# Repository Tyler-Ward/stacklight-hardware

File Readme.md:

POE Stack Light PCB design
==========================

The [POE stack light][blog-post] is a network controlled status indication light that is powered over the network using POE.

This repository contains the Kicad schematic and PCB design for the project, the [firmware][firmware-repo] and [documentation and build guide][documentation-repo] can be found in their respective git repositories.

Circuit Overview
---------------

The design is split into four major sections, the output stage, the POE power supply, the processor, and the network interface.

The stack light takes a common 12v input with switched grounds for each light segment and the buzzer.
A mosfet is used to control each of the channels, brightness is controlled by PWM from the microcontroller.
As supplied the light has a voltage regulator based current limiter shared across all the illumination channels, this prevents multiple segments from being lit at full brightness simultaneously.
This is resolved by bypassing the current limit inside the light with a jumper wire and then adding a copy of the current limiter circuit in the light to the board for each of the three led channels, giving them their own current limit.
See the assembly documentation for how to modify the stack light do this.

For the POE power input, a transformer setup rather than a switch mode design is used.
The use of a transformer based design provides electrical isolation and allows other connections to be exposed without the risk of a short.
The power over ethernet schematic is based on the MP8007 reference design.
A backup DC jack is also available if wanting to build without POE.

An integrated ESP32 wireless module is used for the main processor.
The network interface uses the LAN8710A ethernet transceiver IC.
This communicates to the ESP32 with the RMII protocol used for 100MB ethernet PHYs.
A USB to serial converter is included to facilitate easy programming.

[blog-post]: https://www.scorpia.co.uk/2021/05/23/building-a-poe-enabled-lighting-fixture/
[firmware-repo]: https://github.com/Tyler-Ward/stacklight-firmware
[documentation-repo]: https://github.com/Tyler-Ward/stacklight-documentation

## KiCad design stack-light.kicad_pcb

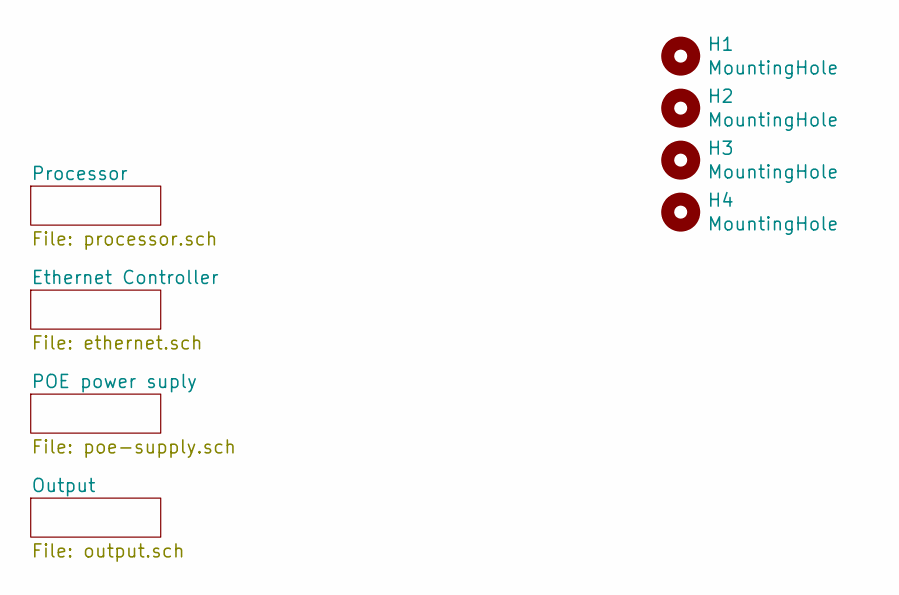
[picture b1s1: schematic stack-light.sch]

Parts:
H1, H2, H3, H4: MountingHole; MountingHole_3.2mm_M3

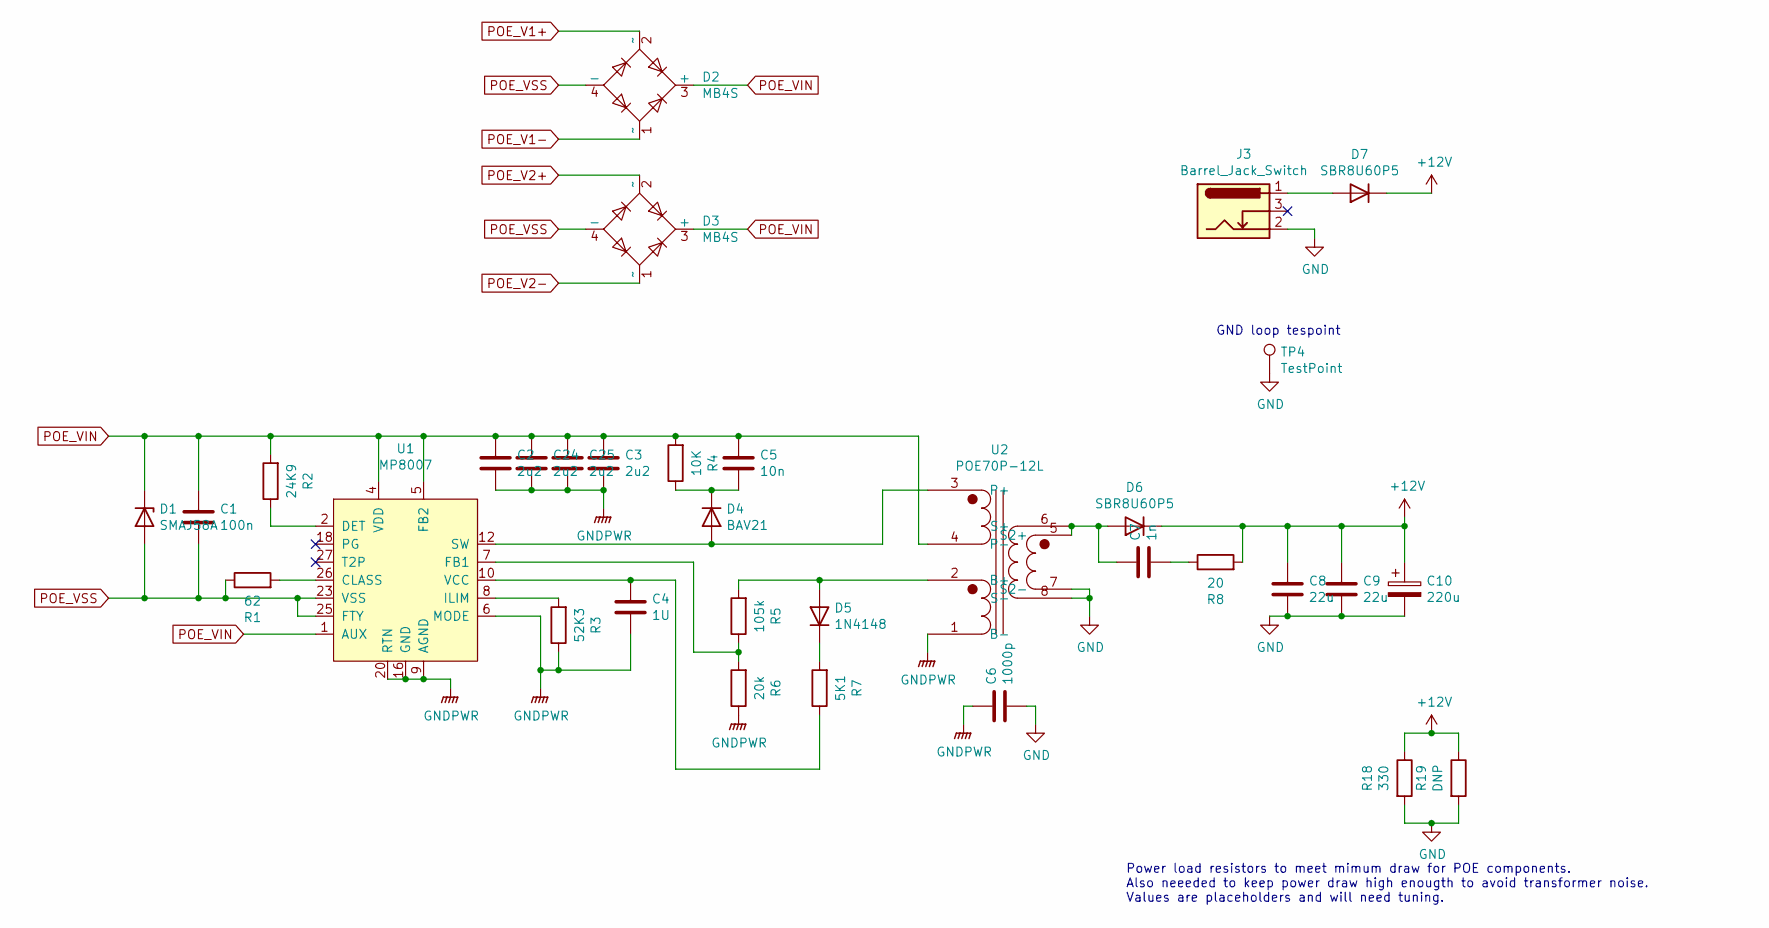
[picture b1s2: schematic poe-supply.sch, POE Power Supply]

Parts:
C1: 100n; C_1206_3216Metric
C2, C3, C24, C25: 2u2; C_1210_3225Metric
C4: 1U; C_0603_1608Metric
C5: 10n; C_0805_2012Metric
C6: 1000p; C_1806_4516Metric
C7: 1n; C_0603_1608Metric
C8, C9: 22u; C_1210_3225Metric
C10: 220u; CP_EIA-7343-31_Kemet-D
D1: SMAJ58A; D_SMA
D2, D3: MB4S; TO-269AA
D4: BAV21; D_SOD-123
D5: 1N4148; D_SOD-323
D6, D7: SBR8U60P5; D_PowerDI-5
J3: Barrel_Jack_Switch; BarrelJack_Horizontal
R1: 62; R_0603_1608Metric
R2: 24K9; R_0603_1608Metric
R3: 52K3; R_0603_1608Metric
R4: 10K; R_1206_3216Metric
R5: 105k; R_0603_1608Metric
R6: 20k; R_0603_1608Metric
R7: 5K1; R_0603_1608Metric
R8: 20; R_0805_2012Metric
R18: 330; R_1210_3225Metric
R19: DNP; R_1210_3225Metric
TP4: TestPoint; TestPoint_Bridge_Pitch5.08mm_Drill0.7mm
U1: MP8007; QFN-28-1EP_4x5mm_P0.5mm_EP2.65x3.65mm
U2: POE70P-12L; Transformer_Coilcraft_POE70P

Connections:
+12V: C8.1, C9.1, C10.1, D6.1 (K), D7.1 (K), R8.2, R18.1, R19.1; also elsewhere on the board
GND: C6.2, C8.2, C9.2, C10.2, J3.2, R18.2, R19.2, TP4.1, U2.7 (S2-), U2.8 (S-); also elsewhere on the board
GNDPWR: C2.2, C3.2, C4.2, C6.1, C24.2, C25.2, R3.1, R6.1, U1.6 (MODE), U1.9 (AGND), U1.16 (GND), U1.17, U1.20 (RTN), U1.21, U1.29 (GND), U2.1 (B-)
unnamed: C4.1, R7.1, U1.10 (VCC)
unnamed: C5.2, D4.1 (K), R4.1
unnamed: C7.1, D6.2 (A), U2.5 (S2+), U2.6 (S+)
unnamed: C7.2, R8.1
unnamed: D4.2 (A), U1.12 (SW), U1.13, U2.3 (P+)
unnamed: D5.1 (K), R7.2
unnamed: D5.2 (A), R5.2, U2.2 (B+)
unnamed: D7.2 (A), J3.1
unnamed: R1.2, U1.26 (CLASS)
unnamed: R2.1, U1.2 (DET)
unnamed: R3.2, U1.8 (ILIM)
unnamed: R5.1, R6.2, U1.7 (FB1)
POE_V1+: D2.2 (~~); also elsewhere on the board
POE_V1-: D2.1 (~~); also elsewhere on the board
POE_V2+: D3.2 (~~); also elsewhere on the board
POE_V2-: D3.1 (~~); also elsewhere on the board
POE_VIN: C1.1, C2.1, C3.1, C5.1, C24.1, C25.1, D1.1 (K), D2.3 (+), D3.3 (+), R2.2, R4.2, U1.1 (AUX), U1.4 (VDD), U1.5 (FB2), U2.4 (P-)
POE_VSS: C1.2, D1.2 (A), D2.4 (-), D3.4 (-), R1.1, U1.23 (VSS), U1.24, U1.25 (FTY)

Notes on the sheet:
Power load resistors to meet mimum draw for POE components. Also neeeded to keep power draw high enougth to avoid transformer noise. Values are placeholders and will need tuning.
GND loop tespoint

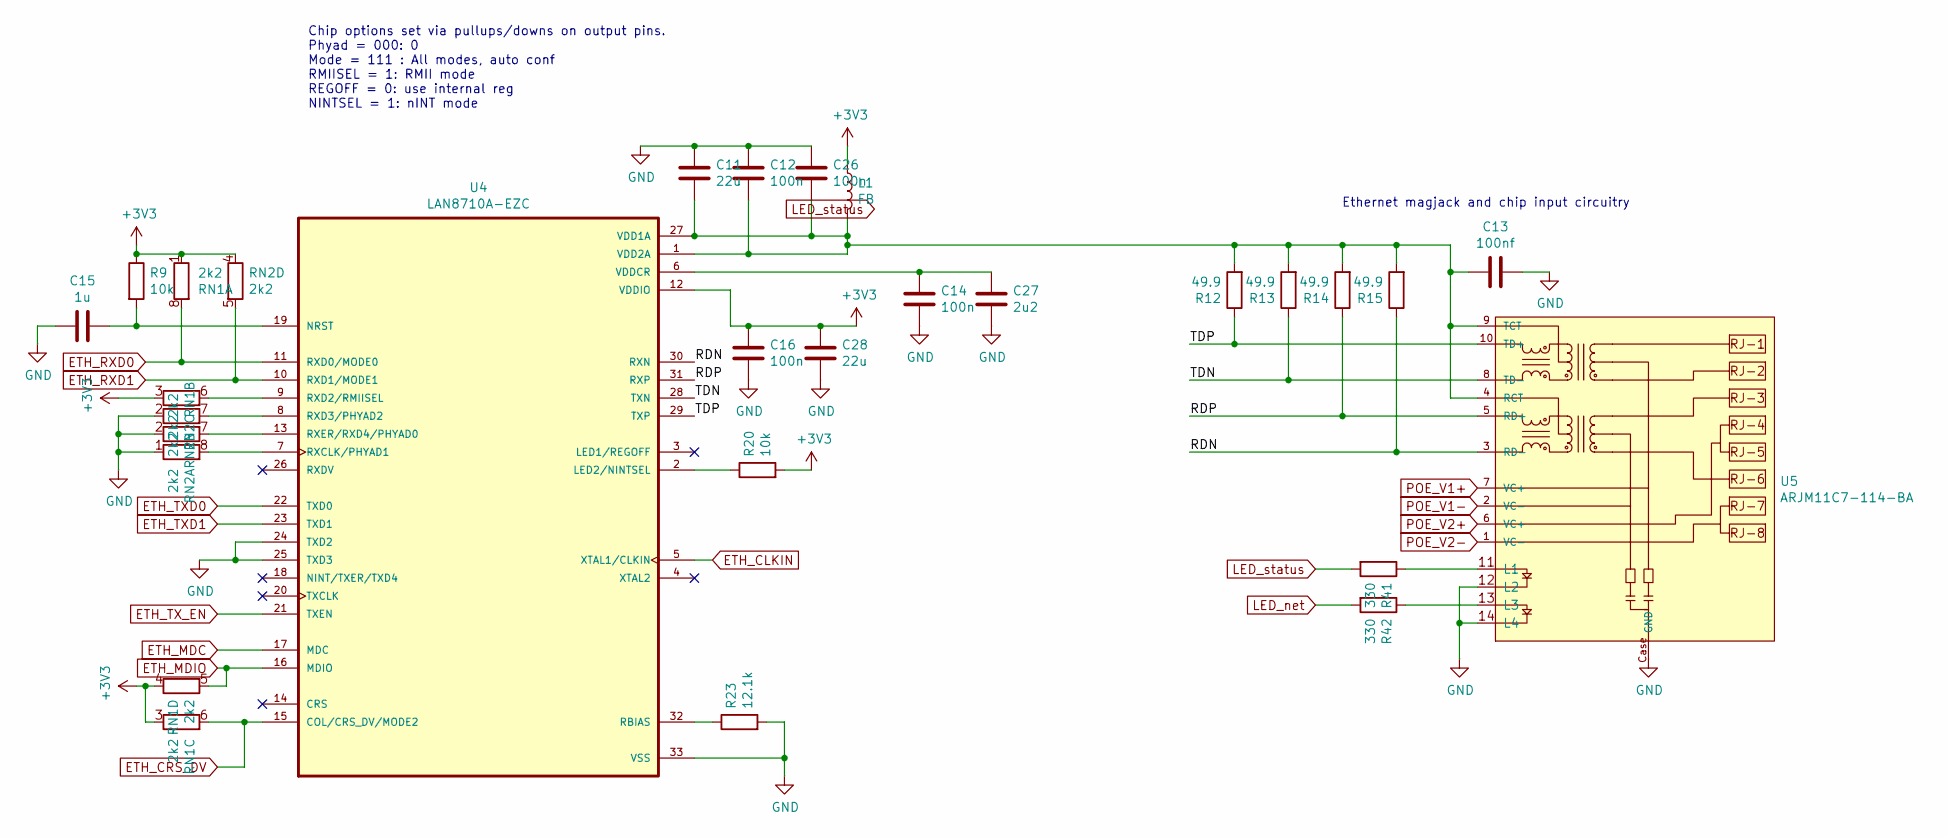
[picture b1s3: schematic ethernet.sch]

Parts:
C11, C28: 22u; C_0805_2012Metric
C12, C14, C16, C26: 100n; C_0603_1608Metric
C13: 100nf; C_0603_1608Metric
C15: 1u; C_0603_1608Metric
C27: 2u2; C_0603_1608Metric
L1: FB; L_0805_2012Metric
R9, R20: 10k; R_0603_1608Metric
R12, R13, R14, R15: 49.9; R_0603_1608Metric
R23: 12.1k; R_0603_1608Metric
R41, R42: 330; R_0603_1608Metric
RN1, RN2: 2k2; R_Array_Convex_4x0603
U4: LAN8710A-EZC; QFN-32-1EP_5x5mm_P0.5mm_EP3.3x3.3mm
U5: ARJM11C7-114-BA

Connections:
+3V3: C16.1, C28.1, L1.1, R9.1, R20.2, RN1.1 (R1.1), RN1.3 (R3.1), RN1.4 (R4.1), RN2.3 (R3.1), RN2.4 (R4.1), U4.12 (VDDIO); also elsewhere on the board
/Ethernet Controller/RDN: R15.1, U4.30 (RXN), U5.3 (RD-)
/Ethernet Controller/RDP: R14.1, U4.31 (RXP), U5.5 (RD+)
/Ethernet Controller/TDN: R13.1, U4.28 (TXN), U5.8 (TD-)
/Ethernet Controller/TDP: R12.1, U4.29 (TXP), U5.10 (TD+)
ETH_CLKIN: U4.5 (XTAL1/CLKIN); also elsewhere on the board
ETH_CRS_DV: RN1.6 (R3.2), U4.15 (COL/CRS_DV/MODE2); also elsewhere on the board
ETH_MDC: U4.17 (MDC); also elsewhere on the board
ETH_MDIO: RN1.5 (R4.2), U4.16 (MDIO); also elsewhere on the board
ETH_RXD0: RN1.8 (R1.2), U4.11 (RXD0/MODE0); also elsewhere on the board
ETH_RXD1: RN2.5 (R4.2), U4.10 (RXD1/MODE1); also elsewhere on the board
ETH_TXD0: U4.22 (TXD0); also elsewhere on the board
ETH_TXD1: U4.23 (TXD1); also elsewhere on the board
ETH_TX_EN: U4.21 (TXEN); also elsewhere on the board
GND: C11.1, C12.1, C13.1, C14.2, C15.2, C16.2, C26.1, C27.2, C28.2, R23.2, RN1.2 (R2.1), RN2.1 (R1.1), RN2.2 (R2.1), U4.24 (TXD2), U4.25 (TXD3), U4.33 (VSS), U5.12 (L2), U5.14 (L4), U5.Case (GND); also elsewhere on the board
LED_net: R42.2; also elsewhere on the board
LED_status: R41.2; also elsewhere on the board
unnamed: C11.2, C12.2, C13.2, C26.2, L1.2, R12.2, R13.2, R14.2, R15.2, U4.1 (VDD2A), U4.27 (VDD1A), U5.4 (RCT), U5.9 (TCT)
unnamed: C14.1, C27.1, U4.6 (VDDCR)
unnamed: C15.1, R9.2, U4.19 (NRST)
unnamed: R20.1, U4.2 (LED2/NINTSEL)
unnamed: R23.1, U4.32 (RBIAS)
unnamed: R41.1, U5.11 (L1)
unnamed: R42.1, U5.13 (L3)
unnamed: RN1.7 (R2.2), U4.13 (RXER/RXD4/PHYAD0)
unnamed: RN2.6 (R3.2), U4.9 (RXD2/RMIISEL)
unnamed: RN2.7 (R2.2), U4.8 (RXD3/PHYAD2)
unnamed: RN2.8 (R1.2), U4.7 (RXCLK/PHYAD1)
POE_V1+: U5.7 (VC+); also elsewhere on the board
POE_V1-: U5.2 (VC-); also elsewhere on the board
POE_V2+: U5.6 (VC+); also elsewhere on the board
POE_V2-: U5.1 (VC-); also elsewhere on the board

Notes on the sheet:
Ethernet magjack and chip input circuitry
Chip options set via pullups/downs on output pins. Phyad = 000: 0 Mode = 111 : All modes, auto conf RMIISEL = 1: RMII mode REGOFF = 0: use internal reg NINTSEL = 1: nINT mode

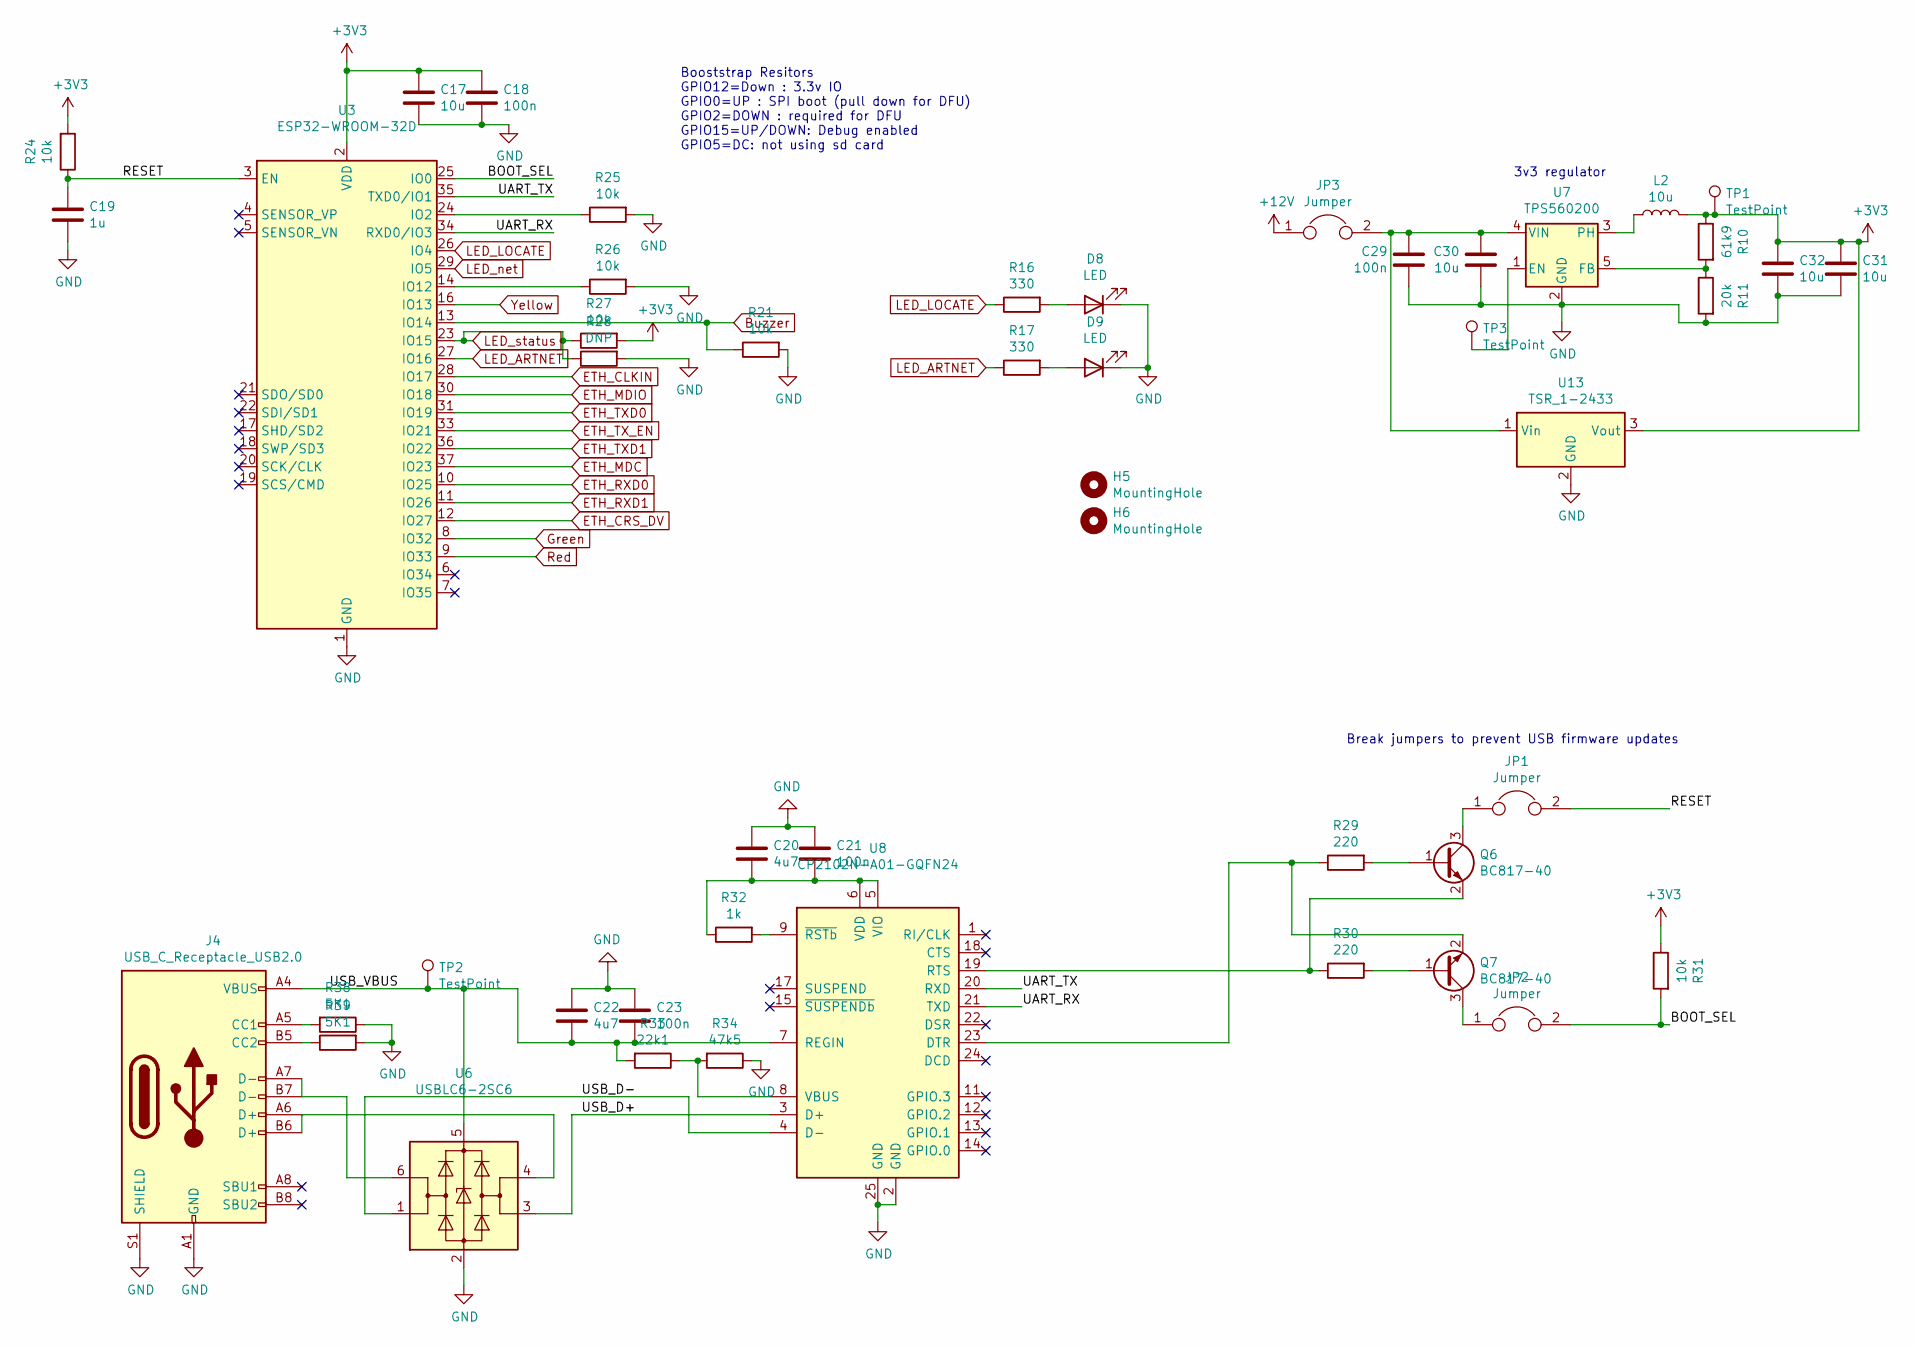
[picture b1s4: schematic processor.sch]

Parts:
C17, C31, C32: 10u; C_0603_1608Metric
C18, C21, C23, C29: 100n; C_0603_1608Metric
C19: 1u; C_0603_1608Metric
C20, C22: 4u7; C_0603_1608Metric
C30: 10u; C_0805_2012Metric
D8, D9: LED; LED_0603_1608Metric
H5, H6: MountingHole; SLP3-150-150-R
J4: USB_C_Receptacle_USB2.0; USB_C_Receptacle_GCT_USB4085
JP1, JP2: Jumper; SolderJumper-2_P1.3mm_Bridged_Pad1.0x1.5mm
JP3: Jumper; SolderJumper-2_P1.3mm_Open_Pad1.0x1.5mm
L2: 10u; L_1008_2520Metric
Q6, Q7: BC817-40; SOT-23
R10: 61k9; R_0603_1608Metric
R11: 20k; R_0603_1608Metric
R16, R17: 330; R_0603_1608Metric
R21, R24, R25, R26, R27, R31: 10k; R_0603_1608Metric
R28: DNP; R_0603_1608Metric
R29, R30: 220; R_0603_1608Metric
R32: 1k; R_0603_1608Metric
R33: 22k1; R_0603_1608Metric
R34: 47k5; R_0603_1608Metric
R38, R39: 5K1; R_0603_1608Metric
TP1, TP2, TP3: TestPoint; TestPoint_Pad_D1.0mm
U3: ESP32-WROOM-32D; ESP32-WROOM-32
U6: USBLC6-2SC6; SOT-23-6
U7: TPS560200; SOT-23-5
U8: CP2102N-A01-GQFN24; QFN-24-1EP_4x4mm_P0.5mm_EP2.6x2.6mm
U13: TSR_1-2433; Converter_DCDC_TRACO_TSR-1_THT

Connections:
+3V3: C17.1, C18.1, C31.1, C32.1, L2.2, R10.1, R24.2, R27.2, R31.1, TP1.1, U3.2 (VDD), U13.3 (Vout); also elsewhere on the board
+12V: JP3.1; also elsewhere on the board
/Processor/BOOT_SEL: JP2.2, R31.2, U3.25 (IO0)
/Processor/RESET: C19.1, JP1.2, R24.1, U3.3 (EN)
/Processor/UART_RX: U3.34 (RXD0/IO3), U8.21 (TXD)
/Processor/UART_TX: U3.35 (TXD0/IO1), U8.20 (RXD)
/Processor/USB_D+: U6.3 (I/O2), U8.3 (D+)
/Processor/USB_D-: U6.1 (I/O1), U8.4 (D-)
/Processor/USB_VBUS: C22.2, C23.2, J4.A4 (VBUS), J4.A9 (VBUS), J4.B4 (VBUS), J4.B9 (VBUS), R33.2, TP2.1, U6.5 (VBUS), U8.7 (REGIN)
Buzzer: R21.1, U3.13 (IO14); also elsewhere on the board
ETH_CLKIN: U3.28 (IO17); also elsewhere on the board
ETH_CRS_DV: U3.12 (IO27); also elsewhere on the board
ETH_MDC: U3.37 (IO23); also elsewhere on the board
ETH_MDIO: U3.30 (IO18); also elsewhere on the board
ETH_RXD0: U3.10 (IO25); also elsewhere on the board
ETH_RXD1: U3.11 (IO26); also elsewhere on the board
ETH_TXD0: U3.31 (IO19); also elsewhere on the board
ETH_TXD1: U3.36 (IO22); also elsewhere on the board
ETH_TX_EN: U3.33 (IO21); also elsewhere on the board
GND: C17.2, C18.2, C19.2, C20.1, C21.1, C22.1, C23.1, C29.2, C30.2, C31.2, C32.2, D8.1 (K), D9.1 (K), J4.A1 (GND), J4.A12 (GND), J4.B1 (GND), J4.B12 (GND), J4.S1 (SHIELD), R11.2, R21.2, R25.2, R26.2, R28.2, R34.1, R38.1, R39.2, U3.1 (GND), U3.15 (GND), U3.38 (GND), U3.39 (GND), U6.2 (GND), U7.2 (GND), U8.2 (GND), U8.25 (GND), U13.2 (GND); also elsewhere on the board
Green: U3.8 (IO32); also elsewhere on the board
LED_ARTNET: R17.1, U3.27 (IO16)
LED_LOCATE: R16.1, U3.26 (IO4)
LED_net: U3.29 (IO5); also elsewhere on the board
LED_status: R27.1, R28.1, U3.23 (IO15); also elsewhere on the board
unnamed: C20.2, C21.2, R32.1, U8.5 (VIO), U8.6 (VDD)
unnamed: C29.1, C30.1, JP3.2, U7.4 (VIN), U13.1 (Vin)
unnamed: D8.2 (A), R16.2
unnamed: D9.2 (A), R17.2
unnamed: J4.A5 (CC1), R38.2
unnamed: J4.A6 (D+), J4.B6 (D+), U6.4 (I/O2)
unnamed: J4.A7 (D-), J4.B7 (D-), U6.6 (I/O1)
unnamed: J4.B5 (CC2), R39.1
unnamed: JP1.1, Q6.3 (C)
unnamed: JP2.1, Q7.3 (C)
unnamed: L2.1, U7.3 (PH)
unnamed: Q6.1 (B), R29.2
unnamed: Q6.2 (E), R30.1, U8.19 (RTS)
unnamed: Q7.1 (B), R30.2
unnamed: Q7.2 (E), R29.1, U8.23 (DTR)
unnamed: R10.2, R11.1, U7.5 (FB)
unnamed: R25.1, U3.24 (IO2)
unnamed: R26.1, U3.14 (IO12)
unnamed: R32.2, U8.9 (~RSTb)
unnamed: R33.1, R34.2, U8.8 (VBUS)
unnamed: TP3.1, U7.1 (EN)
Red: U3.9 (IO33); also elsewhere on the board
Yellow: U3.16 (IO13); also elsewhere on the board

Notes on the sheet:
3v3 regulator
Booststrap Resitors GPIO12=Down : 3.3v IO GPIO0=UP : SPI boot (pull down for DFU) GPIO2=DOWN : required for DFU GPIO15=UP/DOWN: Debug enabled GPIO5=DC: not using sd card
Break jumpers to prevent USB firmware updates

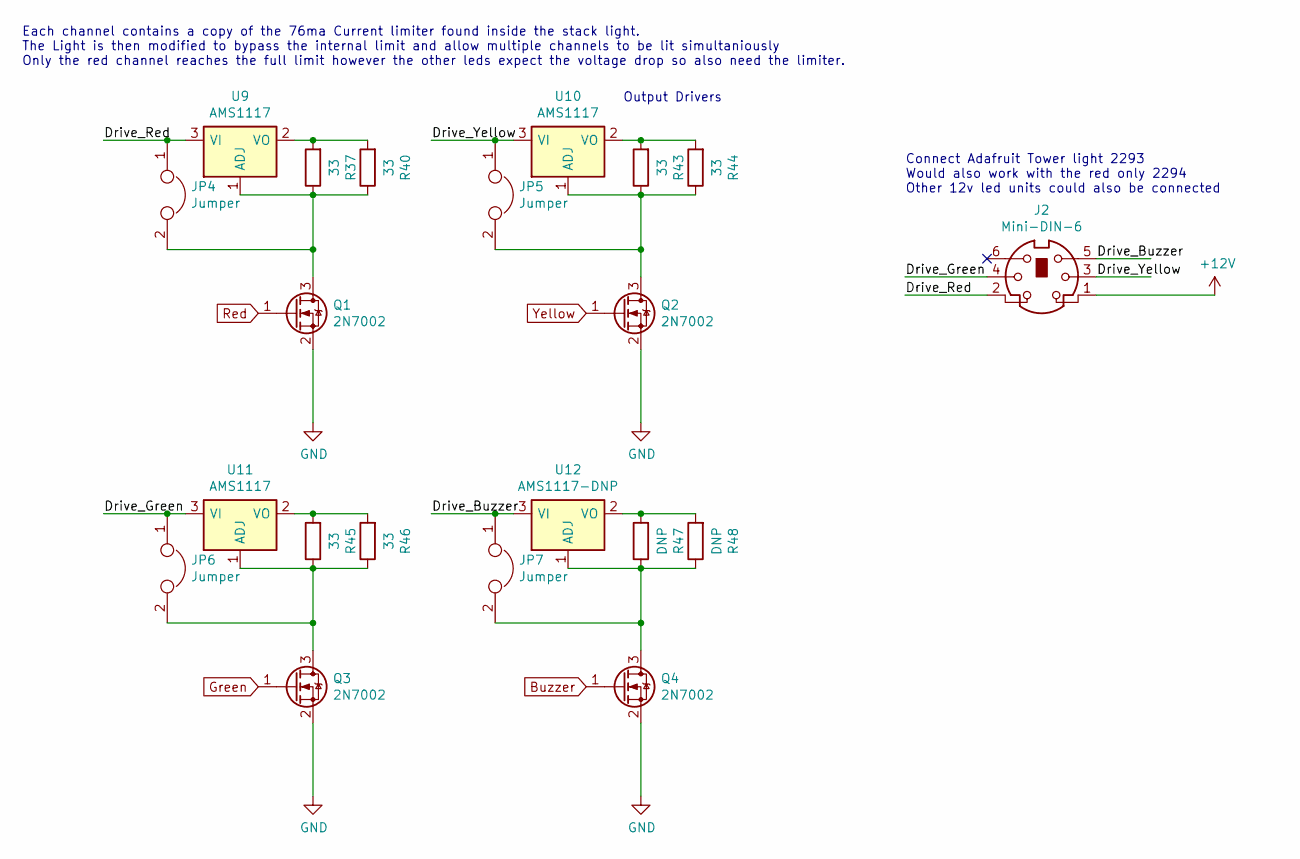
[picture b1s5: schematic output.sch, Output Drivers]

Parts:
J2: Mini-DIN-6; MD60S
JP4, JP5, JP6: Jumper; SolderJumper-2_P1.3mm_Open_Pad1.0x1.5mm
JP7: Jumper; SolderJumper-2_P1.3mm_Bridged_Pad1.0x1.5mm
Q1, Q2, Q3, Q4: 2N7002; SOT-23
R37, R40, R43, R44, R45, R46: 33; R_0603_1608Metric
R47, R48: DNP; R_0603_1608Metric
U9, U10, U11: AMS1117; SOT-223-3_TabPin2
U12: AMS1117-DNP; SOT-223-3_TabPin2

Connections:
+12V: J2.1; also elsewhere on the board
/Output/Drive_Buzzer: J2.5, JP7.1, U12.3 (VI)
/Output/Drive_Green: J2.4, JP6.1, U11.3 (VI)
/Output/Drive_Red: J2.2, JP4.1, U9.3 (VI)
/Output/Drive_Yellow: J2.3, JP5.1, U10.3 (VI)
Buzzer: Q4.1 (G); also elsewhere on the board
GND: Q1.2 (S), Q2.2 (S), Q3.2 (S), Q4.2 (S); also elsewhere on the board
Green: Q3.1 (G); also elsewhere on the board
unnamed: JP4.2, Q1.3 (D), R37.1, R40.1, U9.1 (ADJ)
unnamed: JP5.2, Q2.3 (D), R43.1, R44.1, U10.1 (ADJ)
unnamed: JP6.2, Q3.3 (D), R45.1, R46.1, U11.1 (ADJ)
unnamed: JP7.2, Q4.3 (D), R47.1, R48.1, U12.1 (ADJ)
unnamed: R37.2, R40.2, U9.2 (VO)
unnamed: R43.2, R44.2, U10.2 (VO)
unnamed: R45.2, R46.2, U11.2 (VO)
unnamed: R47.2, R48.2, U12.2 (VO)
Red: Q1.1 (G); also elsewhere on the board
Yellow: Q2.1 (G); also elsewhere on the board

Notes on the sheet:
Output Drivers
Each channel contains a copy of the 76ma Current limiter found inside the stack light. The Light is then modified to bypass the internal limit and allow multiple channels to be lit simultaniously Only the red channel reaches the full limit however the other leds expect the voltage drop so also need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
Connect Adafruit Tower light 2293 Would also work with the red only 2294 Other 12v led units could also be connected

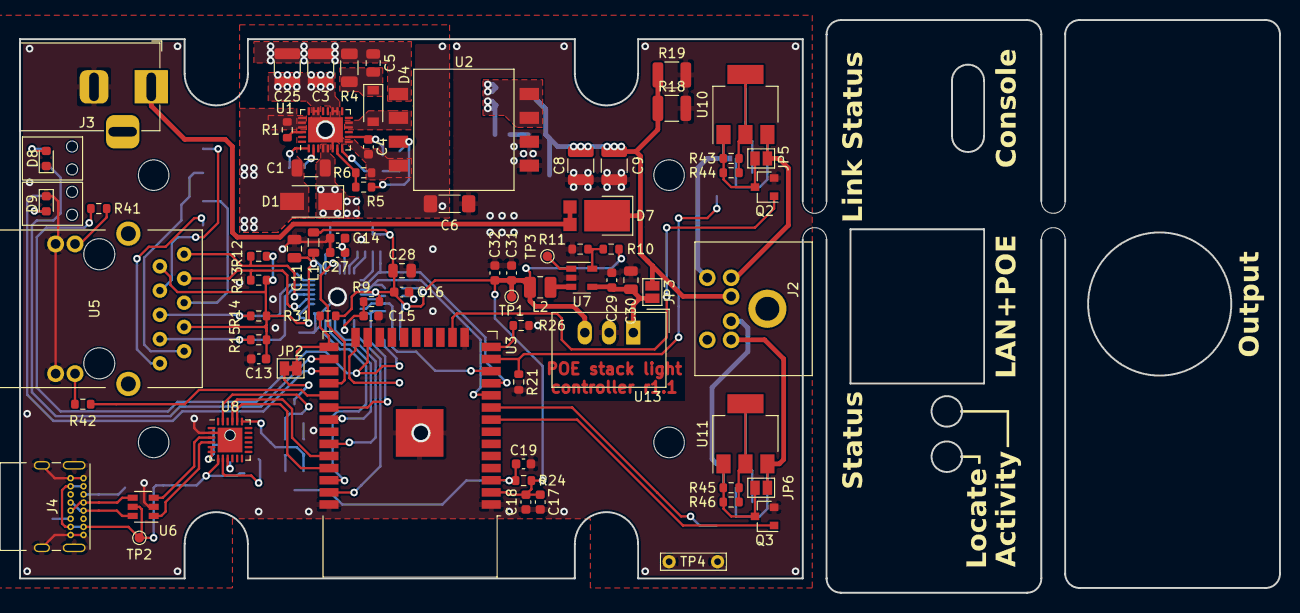
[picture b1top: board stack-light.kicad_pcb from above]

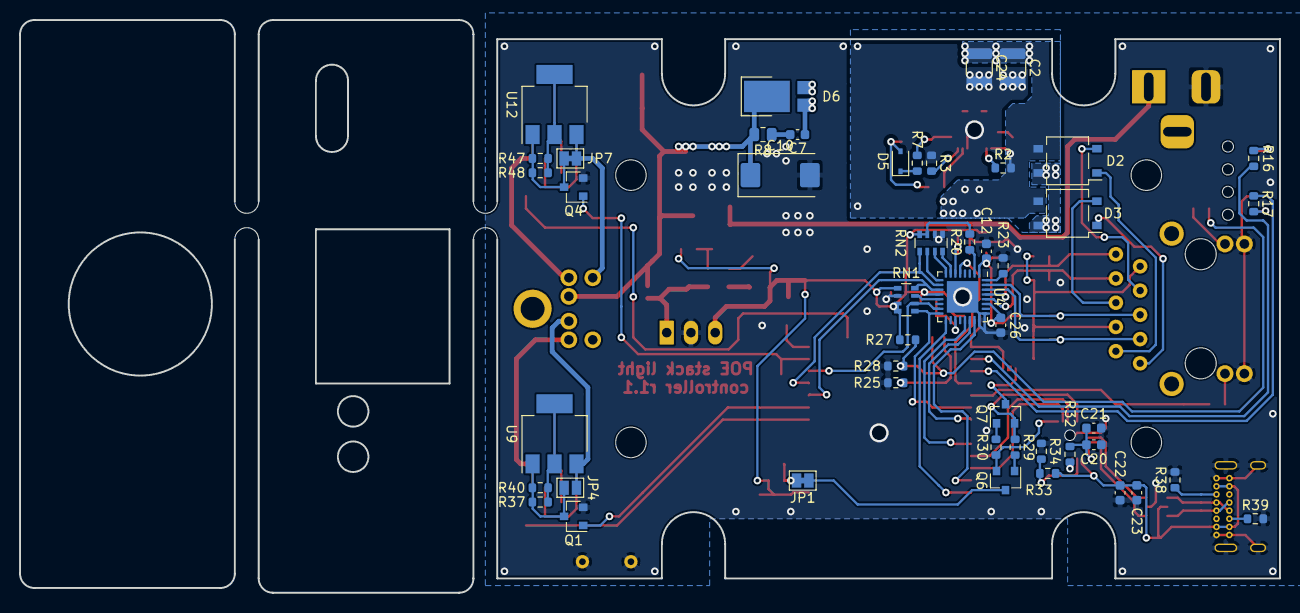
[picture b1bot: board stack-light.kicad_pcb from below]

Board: 2 copper layers, 132.0 x 60.0 mm, 131 parts (48 on the bottom side), 94 nets.

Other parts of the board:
svg2mod: G***; panel_rear
svg2mod#2: G***; panel_front

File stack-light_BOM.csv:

Id,Reference,Package,Quantity,Value,MPN,Digikey,Mouser
50,U5,ARJM11C7-114-BA,1,ARJM11C7-114-BA,ARJM11C7-114-BA,535-14168-ND,815-RJM11C7114BAEW2
60,J3,BarrelJack_Horizontal,1,Barrel_Jack_Switch,,CP-037A-ND,
9,"C31,C32,C17",C_0603_1608Metric,3,10u,,1276-1119-1-ND,
10,"C29,C26,C23,C21,C16,C14,C12,C18,C13",C_0603_1608Metric,8,100n,,1276-1006-1-ND,
21,C27,C_0603_1608Metric,1,2u2,,1276-1183-1-ND,
34,"C22,C20",C_0603_1608Metric,2,4u7,,1276-1045-1-ND,
35,"C15,C19,C4",C_0603_1608Metric,2,1u,,1276-1946-1-ND,
66,C7,C_0603_1608Metric,1,1n,,1276-1131-1-ND,
6,C30,C_0805_2012Metric,1,10u,,587-2189-1-ND,
20,"C28,C11",C_0805_2012Metric,2,22u,,1276-1100-1-ND,
29,C5,C_0805_2012Metric,1,10n,,490-1652-1-ND,
30,C1,C_1206_3216Metric,1,100n,,490-3364-1-ND,
22,"C3,C24,C25,C2",C_1210_3225Metric,4,2u2,,1276-3362-1-ND,
27,"C9,C8",C_1210_3225Metric,2,22u,,1276-1101-1-ND,
28,C6,C_1806_4516Metric,1,1000p,,490-8145-1-ND,
26,C10,CP_EIA-7343-31_Kemet-D,1,220u,,399-10429-1-ND,
60,"D7,D6",D_PowerDI-5,2,SBR8U60P5,SBR8U60P5,SBR8U60P5DICT-ND,621-SBR8U60P5-13
65,D1,D_SMA,1,SMAJ58A,SMAJ58A,SMAJ58ALFCT-ND,652SMAJ58A
63,D4,D_SOD-123,1,BAV21,BAV21,BAV21W-FDICT-ND,621BAV21WF
25,D5,D_SOD-323,1,1N4148,1N4148,1N4148WS-FDICT-ND,6211N4148WSF
46,U3,ESP32-WROOM-32,1,ESP32-WROOM-32D,ESP32-WROOM-32D,1965-ESP32-WROOM-32D(4MB)CT-ND,356-ESPWROOM3200PS3
19,L1,L_0805_2012Metric,1,FB,,2184-BBPY00201209601Y00CT-ND,
11,L2,L_1008_2520Metric,1,10u,,587-2189-6-ND,
61,"D9,D8",LED_0603_1608Metric,2,LED,,160-1435-1-ND,
47,J2,MD60S,1,Mini-DIN-6,MD60S,CP-2460-ND,490-MD-60S
31,U8,QFN-24-1EP_4x4mm_P0.5mm_EP2.6x2.6mm,1,CP2102N-A01-GQFN24,CP2102N-A01-GQFN24,336-5887-ND,634CP2102NA02GQFN24
51,U1,QFN-28-1EP_4x5mm_P0.5mm_EP2.65x3.65mm,1,MP8007,MP8007,1589-1727-1-ND,946-MP8007GV-Z
17,U4,QFN-32-1EP_5x5mm_P0.5mm_EP3.3x3.3mm,1,LAN8710A-EZC,LAN8710A-EZC,LAN8710A-EZC-ABC-ND,579LAN8710AEZCABC
1,"R21,R27,R24,R31,R26,R25,R20,R9",R_0603_1608Metric,8,10k,,CR0603-FX-1002ELFCT-ND,
7,"R17,R16,R42,R41",R_0603_1608Metric,4,330,,311-330HRCT-ND,71-CRCW060333R0FKEAC
12,R10,R_0603_1608Metric,1,61k9,,P61.9KHCT-ND,
32,R34,R_0603_1608Metric,1,47k5,,P47.5KHCT-ND,
33,R33,R_0603_1608Metric,1,22k1,,P22.1KHCT-ND,
38,R32,R_0603_1608Metric,1,1k,,541-1.00KHCT-ND,71-CRCW06031K00JNEAC
39,"R30,R29",R_0603_1608Metric,2,220,,541-220HCT-ND,
41,R23,R_0603_1608Metric,1,12.1k,,541-CRCW060312K1FKEBCT-ND,
42,"R15,R14,R13,R12",R_0603_1608Metric,4,49.9,,P49.9HCT-ND,
52,"R46,R45,R44,R43,R40,R37",R_0603_1608Metric,6,33,,P33.0HCT-ND,
53,"R39,R38,R7",R_0603_1608Metric,2,5K1,,P5.10KHCT-ND,71-CRCW06035K10FKEAC
13,"R6,R11",R_0603_1608Metric,2,20k,,P20.0KHCT-ND,603-RC0603FR-0720KL
55,R5,R_0603_1608Metric,1,105k,,P105KHCT-ND,
56,R3,R_0603_1608Metric,1,52K3,,P52.3KHCT-ND,
57,R2,R_0603_1608Metric,1,24K9,,P24.9KHCT-ND,
58,R1,R_0603_1608Metric,1,62,,P62.0HCT-ND,
23,R8,R_0805_2012Metric,1,20,,RMCF0805FT20R0CT-ND,
24,R4,R_1206_3216Metric,1,10k,,RMCF0805FT20R0CT-ND,
3,R18,R_1210_3225Metric,1,330,,408-1913-1-ND,
18,"RN2,RN1",R_Array_Convex_4x0603,2,2k2,,Y9222CT-ND,667EXB38V222JV
15,"H6,H5",SLP3-150-150-R,2,MountingHole,SLP3-150-150-R,492-2516-ND,749-SLP3150150R
49,"U11,U10,U9",SOT-223-3_TabPin2,3,AMS1117,AMS1117,AZ1117CH-ADJTRG1DICT-ND,621-AZ1117CH-ADJTRG1
43,"Q7,Q6",SOT-23,2,BC817-40,BC817-40,1727-2919-1-ND,771BC81740T/R
59,"Q4,Q3,Q2,Q1",SOT-23,4,2N7002,2N7002,1727-8643-1-ND,7712N7002NXAKR
14,U7,SOT-23-5,1,TPS560200,TPS560200DBVT,296-39566-1-ND,595-TPS560200DBVT
37,U6,SOT-23-6,1,USBLC6-2SC6,USBLC6-2SC6,497-5235-1-ND,511USBLC62SC6
64,"D3,D2",TO-269AA,2,MB4S,MB4S,MB4S-TPMSCT-ND,833-MB4S-TP
4,U2,Transformer_Coilcraft_POE70P,1,POE70P-12L,POE70P-12L,,994-POE70P-12LD
45,J4,USB_C_Receptacle_GCT_USB4085,1,USB_C_Receptacle_USB2.0,USB4085-GF-A,2073-USB4085-GF-ACT-ND,640USB4085GFA
,Case,,1,1593LBK,1593LBK,HM962-ND,546-1593LBK

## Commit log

2021-02-28 Add revision 1.0 of the PCB to git
2021-03-01 Clean up rescued symbols and reneabled layer visibility
2021-04-25 Corrected Footprint for POE transformers, PCB updated for correct footprint
    The POE transformer had the order of its pinout on the higher numbered side reversed so the pairs of output pins were connected back to front. This change fixes this
2021-04-25 Remove note on needing to check POE feedback resistors.
    This change also caused kicad to update the cache to use non rescue components
2021-05-20 Add minor fixes for r1.0 issues
    Add load resistors for POE power supply
    Add pulldown for buzzer output channel
    Mark debug boot resistor as DNP
2021-05-20 Add schematic edits to PCB
    Add load resistors for POE power supply
    Add pulldown for buzzer output channel
2021-05-21 Update readme and add licence
2021-06-20 Add BOM and kitspace.yaml
2021-06-22 Update Readme to include more information on the project and circuitry
2021-06-23 Update kistpace metadata and covert BOM to CSV
2021-06-23 Remove Excel BOM file
2021-08-16 Fix small power supply issues
    Update POE class resistor to 62 ohms (class 2)
    Increase auxiliary winding limit resistor to 5.1k to comply with device current clamp limit
    Add Ground test loop
2021-08-16 Reduce case screw notch size and placement to better match case
    Also center the mini-din output connector
2021-08-16 Adjust front IO to work with a flush panel
    also removed the LED enable transistor
2021-08-16 Remove LED control transistor from BOM
2021-08-17 Add option for SIL regulator module due to component shortage
2021-08-21 Add PCB end panels
2021-08-21 Adjust USB connector hole size to match FAB requirements
2021-08-21 Bump revision to r1.2
    Also perform minor silkscreen cleanup
